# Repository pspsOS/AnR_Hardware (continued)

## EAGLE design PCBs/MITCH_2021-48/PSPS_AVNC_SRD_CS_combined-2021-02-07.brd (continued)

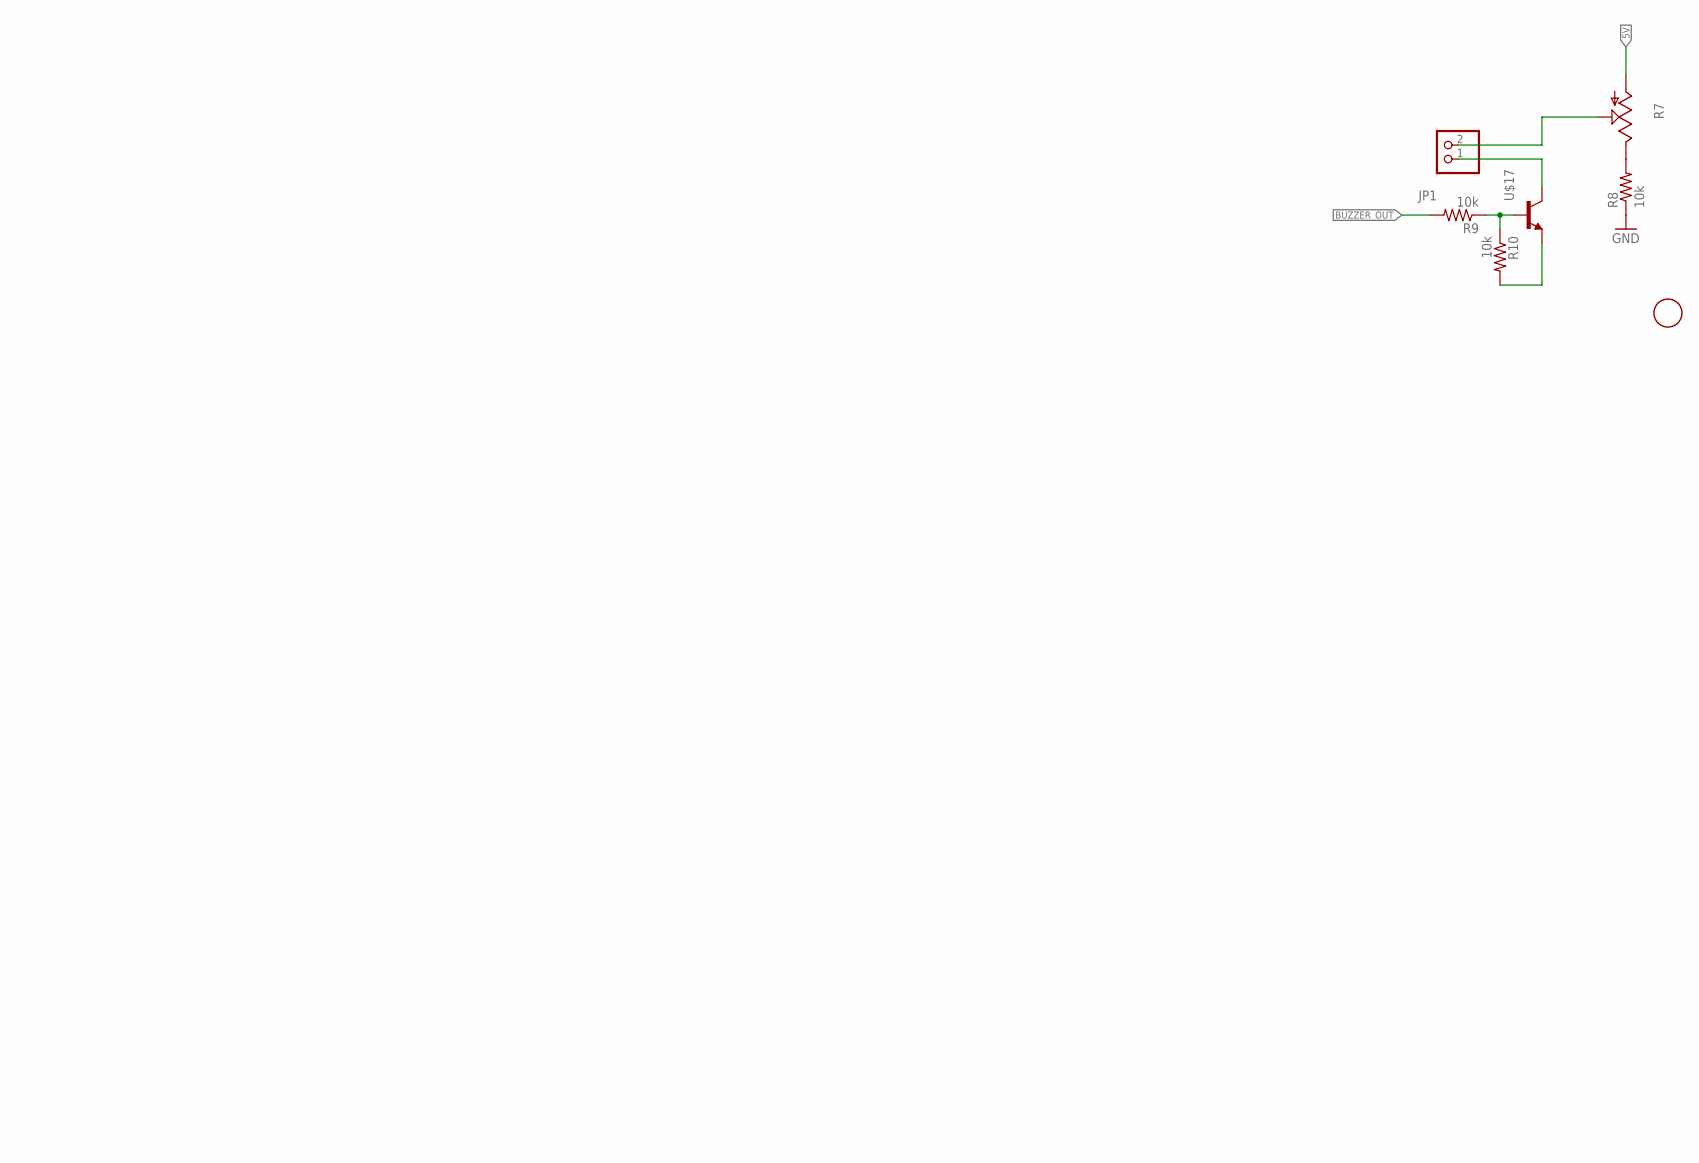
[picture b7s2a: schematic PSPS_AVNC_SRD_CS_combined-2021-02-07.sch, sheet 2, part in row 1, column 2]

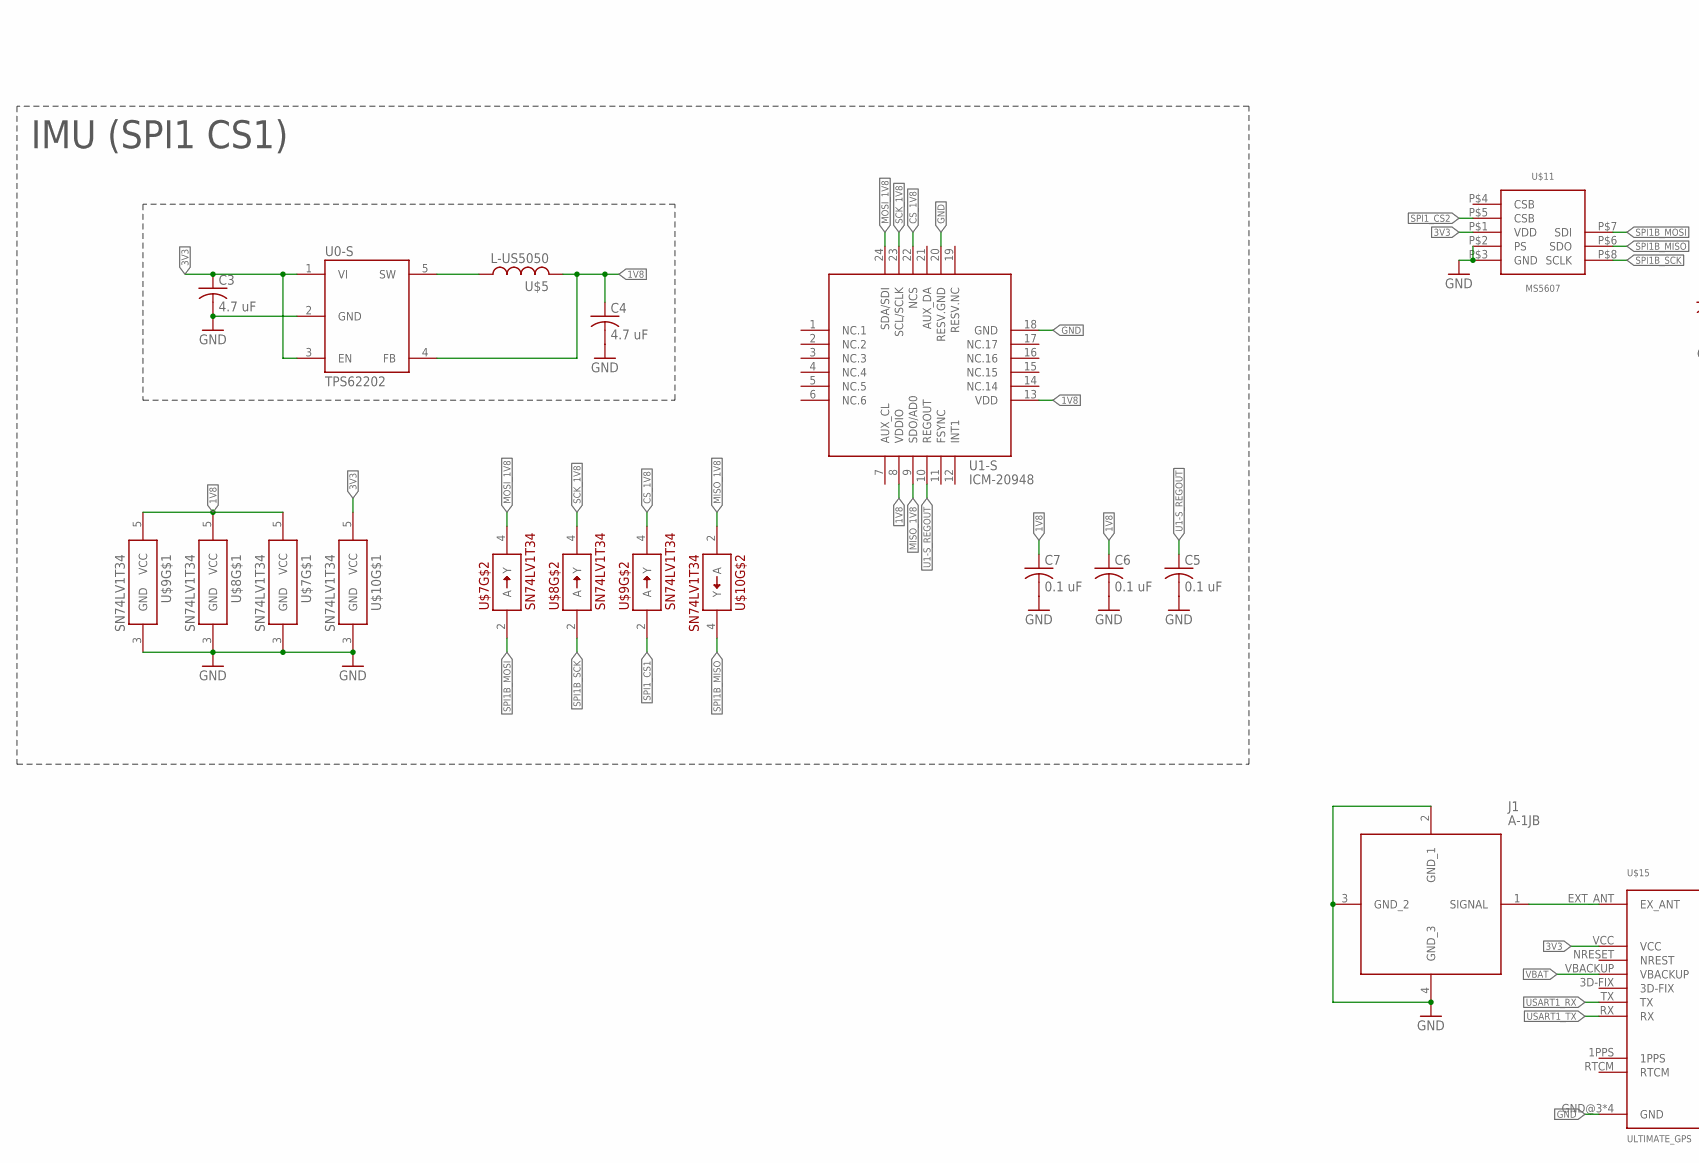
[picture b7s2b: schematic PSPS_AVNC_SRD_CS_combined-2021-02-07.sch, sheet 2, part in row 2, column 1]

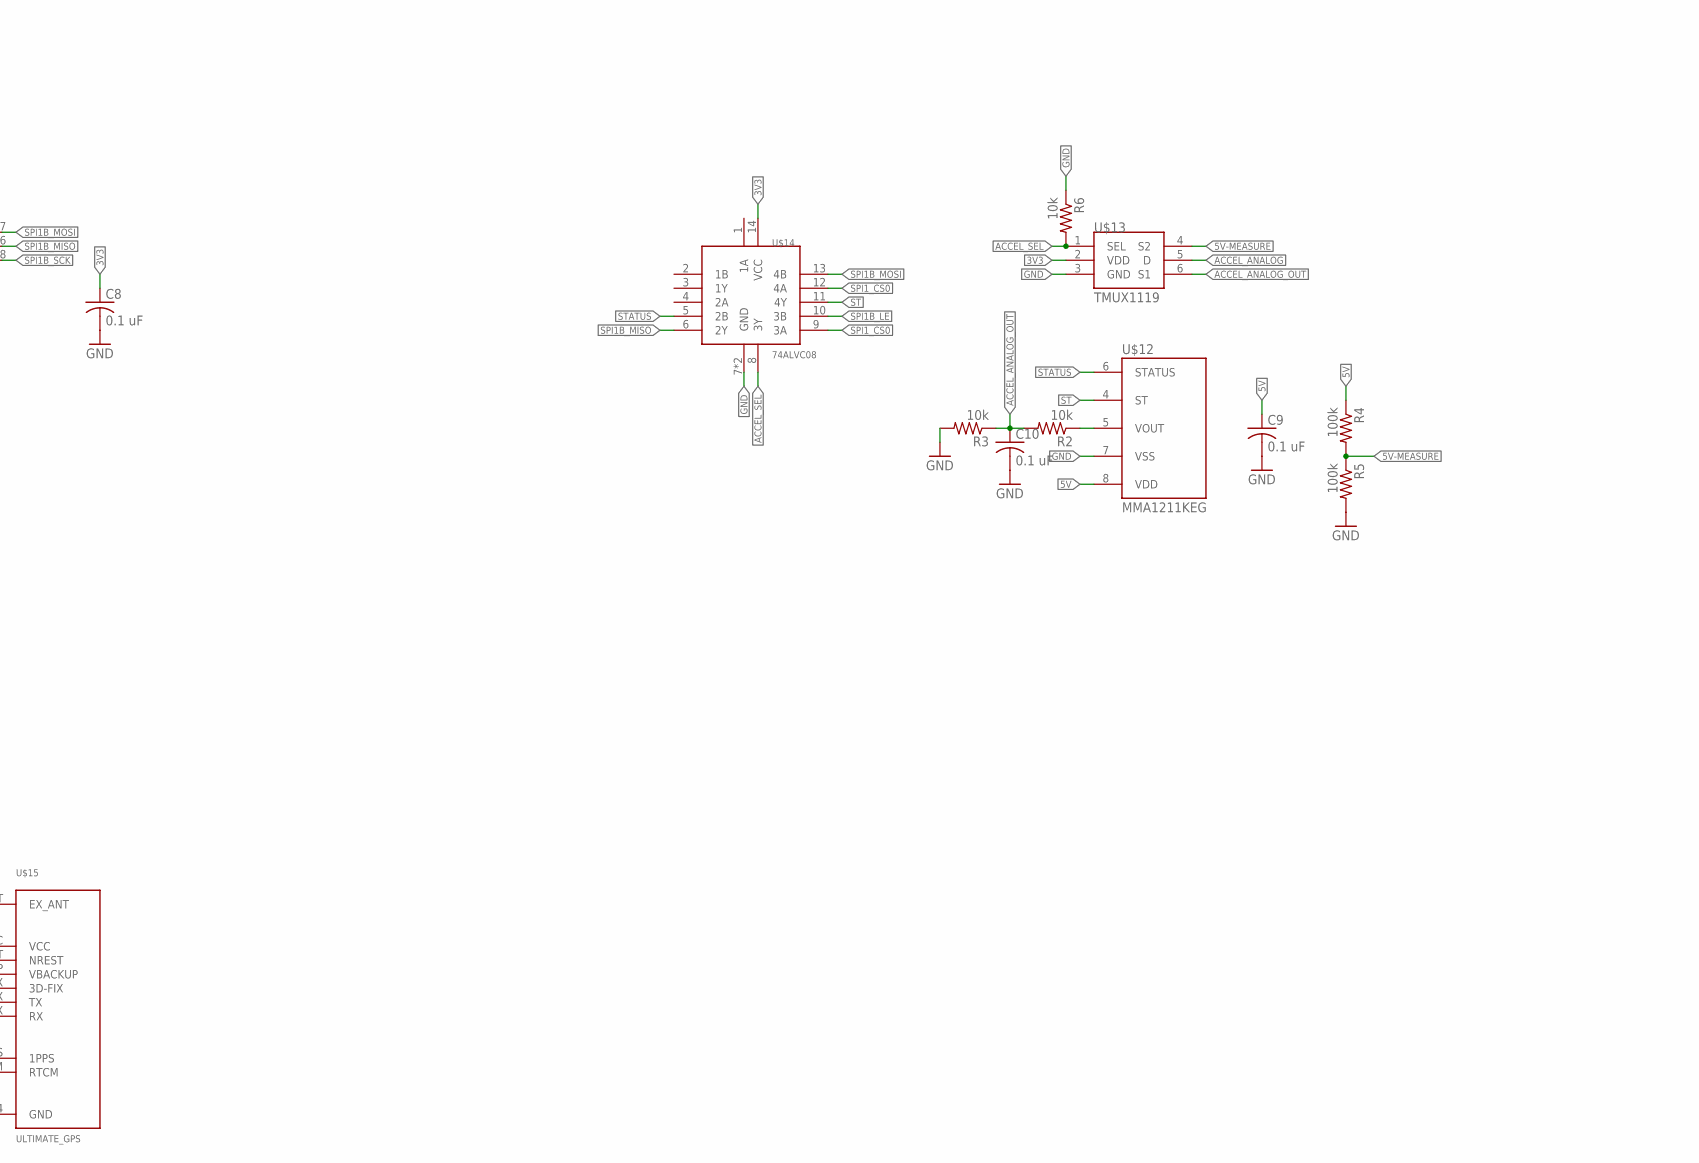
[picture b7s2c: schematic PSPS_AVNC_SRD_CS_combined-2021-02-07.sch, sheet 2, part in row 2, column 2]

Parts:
C3, C4: 4.7 uF; C0805
C5, C6, C7, C8, C9, C10: 0.1 uF; C0805
J1: A-1JB; A1JB
JP1: PINHD-1X2; 1X02
R2, R3, R6, R8, R9, R10: 10k; M0805
R4, R5: 100k; M0805
R7: TRIM_US-LI10; LI10
U0-S: TPS62202; SOT95P280X145-5
U1-S: ICM-20948; QFN40P300X300X105-25T159X175
U$5: L-US5050; INDDFN1250X1250X600-2N
U$7, U$8, U$9, U$10: SN74LV1T34; SOT65P210X110-5
U$11: MS5607
U$12: MMA1211KEG; SOIC127P1041X355-16N
U$13: TMUX1119; SOP95P280X145-6N
U$14: 74ALVC08; QFN50P300X250X100-15T150X100N
U$15: ULTIMATE_GPS; FGPMMOPA6H
U$16: UXCELL_BUZZER
U$17: NPN_TRANSISTOR; SOT23

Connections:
1V8: C4.1, C6.1, C7.1, U0-S.4 (FB), U1-S.8 (VDDIO), U1-S.13 (VDD), U$5.2, U$7.5 (VCC), U$8.5 (VCC), U$9.5 (VCC)
3V3: C3.1, C8.1, U0-S.1 (VI), U0-S.3 (EN), U$10.5 (VCC), U$11.P$1 (VDD), U$13.2 (VDD), U$14.14 (VCC), U$15.VCC; also elsewhere on the board
5V: C9.1, R4.1, R7.A, U$12.8 (VDD)
5V-MEASURE: R4.2, R5.1, U$13.4 (S2)
ACCEL_ANALOG: U$13.5 (D); also elsewhere on the board
ACCEL_ANALOG_OUT: C10.1, R2.2, R3.1, U$13.6 (S1)
ACCEL_SEL: R6.2, U$13.1 (SEL), U$14.8 (3Y)
BUZZER_OUT: R9.2; also elsewhere on the board
CS_1V8: U1-S.22 (NCS), U$9.4 (Y)
EXT-ANT: J1.1 (SIGNAL), U$15.EXT_ANT (EX_ANT)
GND: C3.2, C4.2, C5.2, C6.2, C7.2, C8.2, C9.2, C10.2, J1.2 (GND_1), J1.3 (GND_2), J1.4 (GND_3), R3.2, R5.2, R6.1, R8.1, U0-S.2 (GND), U1-S.18 (GND), U1-S.20 (RESV.GND), U$7.3 (GND), U$8.3 (GND), U$9.3 (GND), U$10.3 (GND), U$11.P$2 (PS), U$11.P$3 (GND), U$12.7 (VSS), U$13.3 (GND), U$14.7 (GND), U$14.15 (GND), U$15.GND@3 (GND), U$15.GND@8 (GND), U$15.GND@12 (GND), U$15.GND@19 (GND); also elsewhere on the board
MISO_1V8: U1-S.9 (SDO/AD0), U$10.2 (A)
MOSI_1V8: U1-S.24 (SDA/SDI), U$7.4 (Y)
unnamed: JP1.2, R7.S
unnamed: JP1.1, U$17.2 (C)
unnamed: R7.E, R8.2
unnamed: R9.1, R10.1, U$17.1 (B)
unnamed: R10.2, U$17.3 (E)
SCK_1V8: U1-S.23 (SCL/SCLK), U$8.4 (Y)
SPI1B_LE: U$14.10 (3B); also elsewhere on the board
SPI1B_MISO: U$10.4 (Y), U$11.P$6 (SDO), U$14.6 (2Y); also elsewhere on the board
SPI1B_MOSI: U$7.2 (A), U$11.P$7 (SDI), U$14.13 (4B); also elsewhere on the board
SPI1B_SCK: U$8.2 (A), U$11.P$8 (SCLK); also elsewhere on the board
SPI1_CS0: U$14.9 (3A), U$14.12 (4A); also elsewhere on the board
SPI1_CS1: U$9.2 (A); also elsewhere on the board
SPI1_CS2: U$11.P$5 (CSB); also elsewhere on the board
ST: U$12.4 (ST), U$14.11 (4Y)
STATUS: U$12.6 (STATUS), U$14.5 (2B)
U0-S_SW: U0-S.5 (SW), U$5.1
U0-S_VOUT: R2.1, U$12.5 (VOUT)
U1-S_REGOUT: C5.1, U1-S.10 (REGOUT)
USART1_RX: U$15.TX; also elsewhere on the board
USART1_TX: U$15.RX; also elsewhere on the board
VBAT: U$15.VBACKUP; also elsewhere on the board

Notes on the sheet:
IMU (SPI1 CS1)

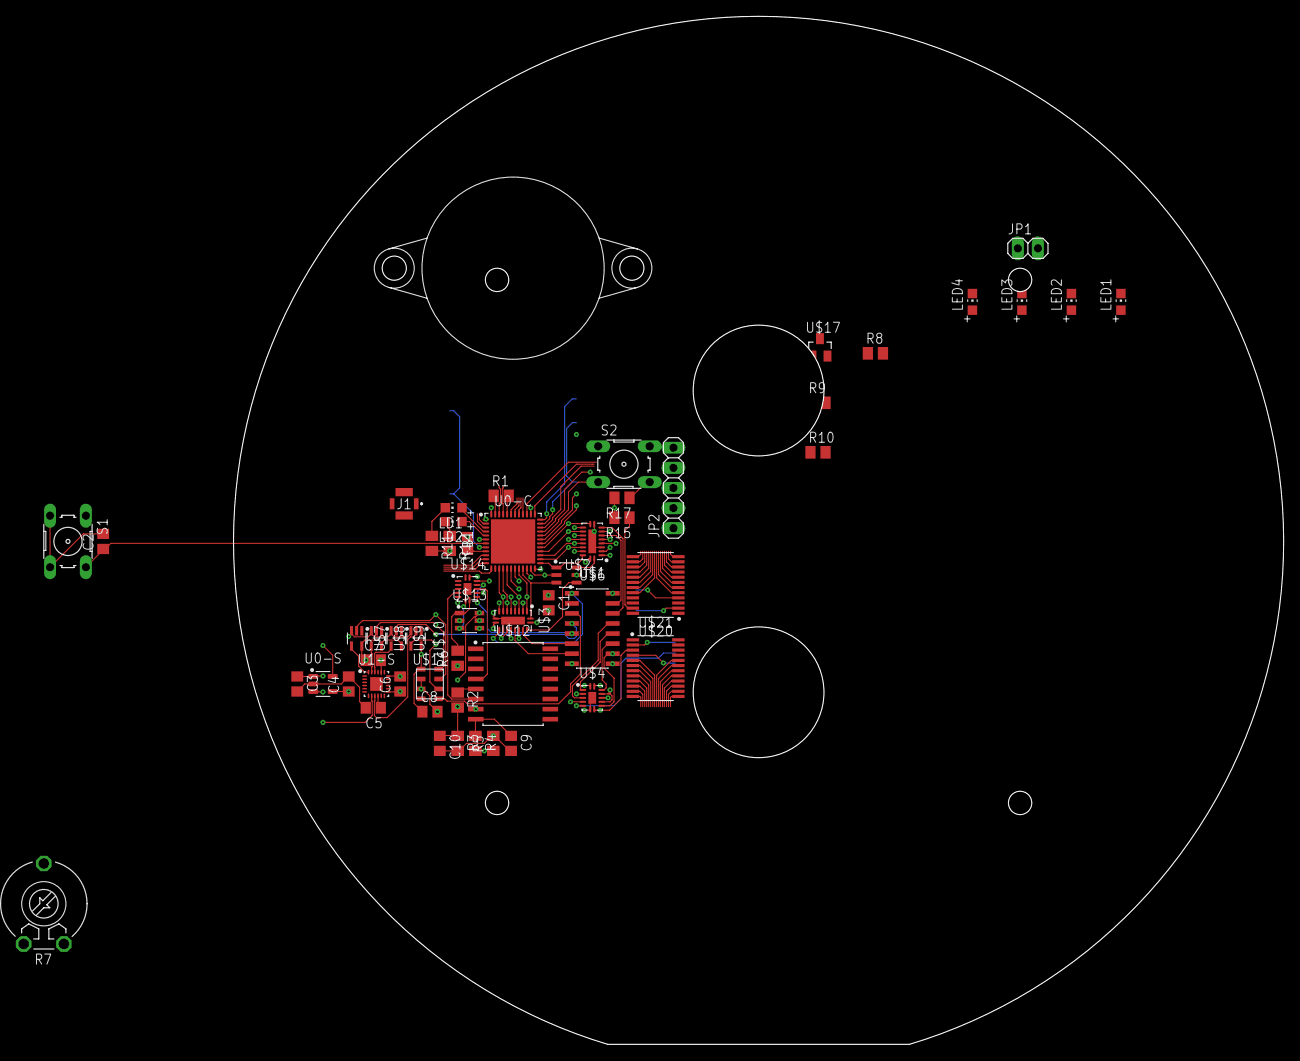
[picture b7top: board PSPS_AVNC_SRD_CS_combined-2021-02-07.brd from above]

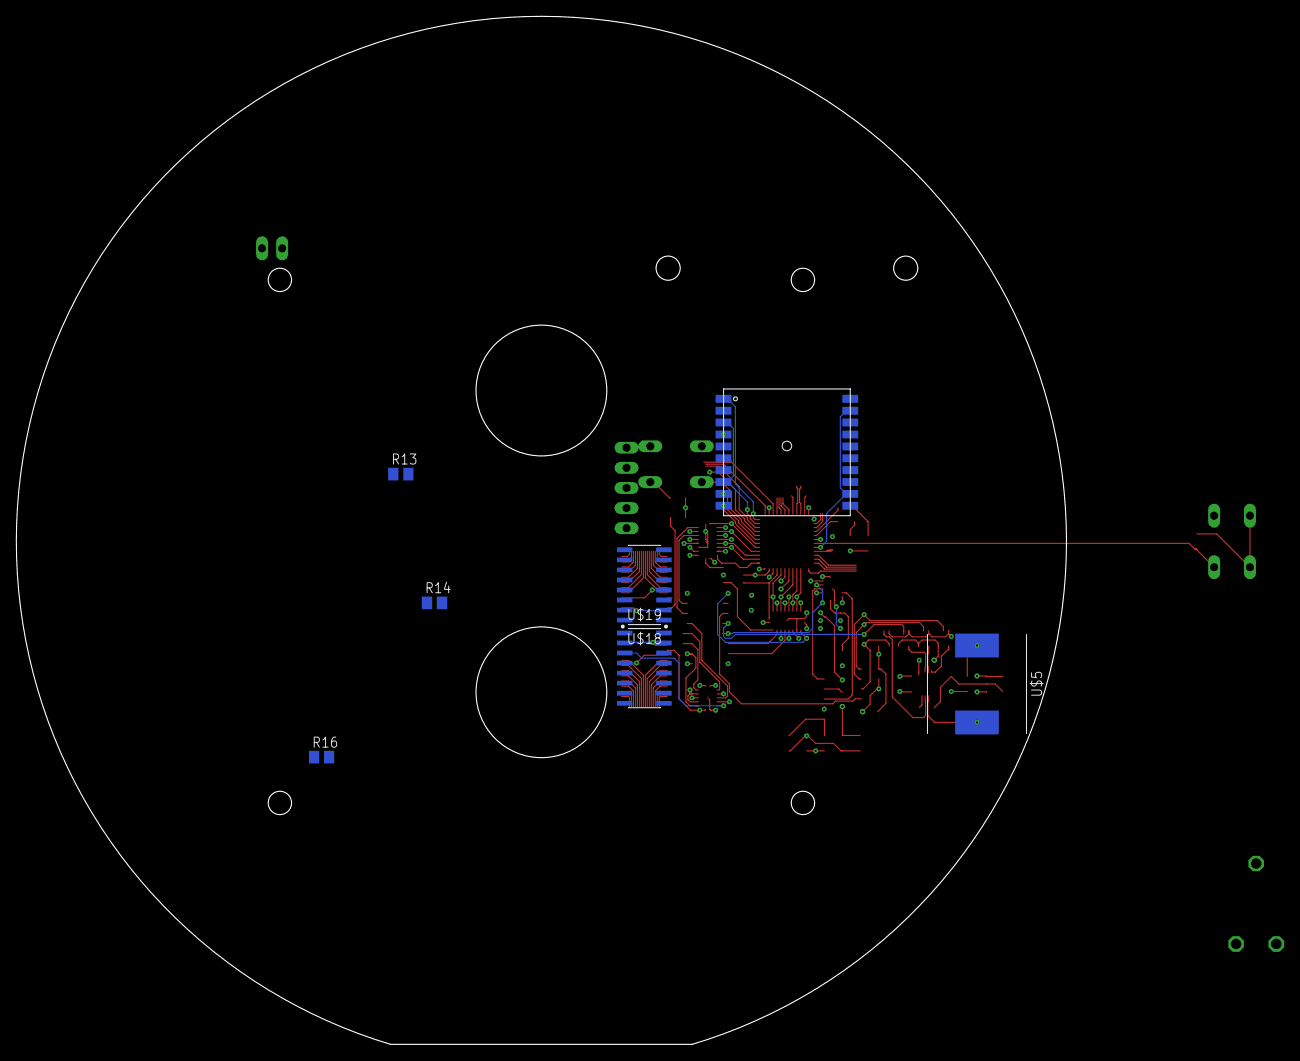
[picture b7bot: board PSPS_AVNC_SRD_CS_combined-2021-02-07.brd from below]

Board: 4 copper layers, 132.6 x 129.8 mm, 63 parts (7 on the bottom side), 77 nets.

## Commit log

2021-02-17 Added hardware files
2021-02-24 Finished Flight Ready PCB Draft
2021-02-24 Updated silk screen
2021-02-24 Final tweaks for MITCH 2021.0
2021-02-25 Continued refining MITCH 2021.0
2021-02-26 Completed MITCH 2021.0 PCB. Ready for review
2021-03-03 MITCH 2021.0 with connector is ready for review
2021-03-03 Added separation notches
2021-03-07 Improved Battery board interface nets
2021-03-13 Battery Board Files Set up. Schematic Worked on for Battery Board
2021-03-15 Added Battery Undervoltage Protection, Still need to ensure this setup is okay
2021-03-16 Fixed the GND_OUT / 3V3 Nets
2021-03-16 Specced out new mosfet and added.
2021-03-16 Buck Converter Obtained (Switching frequency not)
2021-03-16 started the pcb
2021-03-17 Boost/Buck Completed, PCB Started
2021-03-17 added switch jumper
2021-03-17 Added USB and 16-pin
2021-03-17 Added JSTPH2
2021-03-18 Moved MITCH files to own folder
2021-03-18 Created top side PDF part guide
2021-03-19 Further development
2021-03-19 "Round one of PCB" -Mark Paral 2021
2021-03-19 Added LED Colors to MITCH 2021-0
2021-03-21 Further PCB Routing
2021-03-23 Finished Schematic Pin Connections
2021-03-23 Routed everything besides the pinheaders
2021-03-25 minor additional routing
2021-03-26 New transistor design started
2021-04-02 Battery Board work done
2021-04-02 further development. No airwires left
2021-04-06 Touch up before final review
2021-04-07 Routed draft
2021-04-18 Started shield
2021-04-18 updated shield schematic
2021-04-18 Further shield development
2021-04-19 added boost buck to mitch shield
2021-04-25 Shield board stuff
2021-04-26 stuff
2021-04-26 Routed most of mitch shield
2021-04-27 further shield progress
2021-04-27 Shield ready for production?
2021-04-27 ALA Ready
2021-04-27 refined design
